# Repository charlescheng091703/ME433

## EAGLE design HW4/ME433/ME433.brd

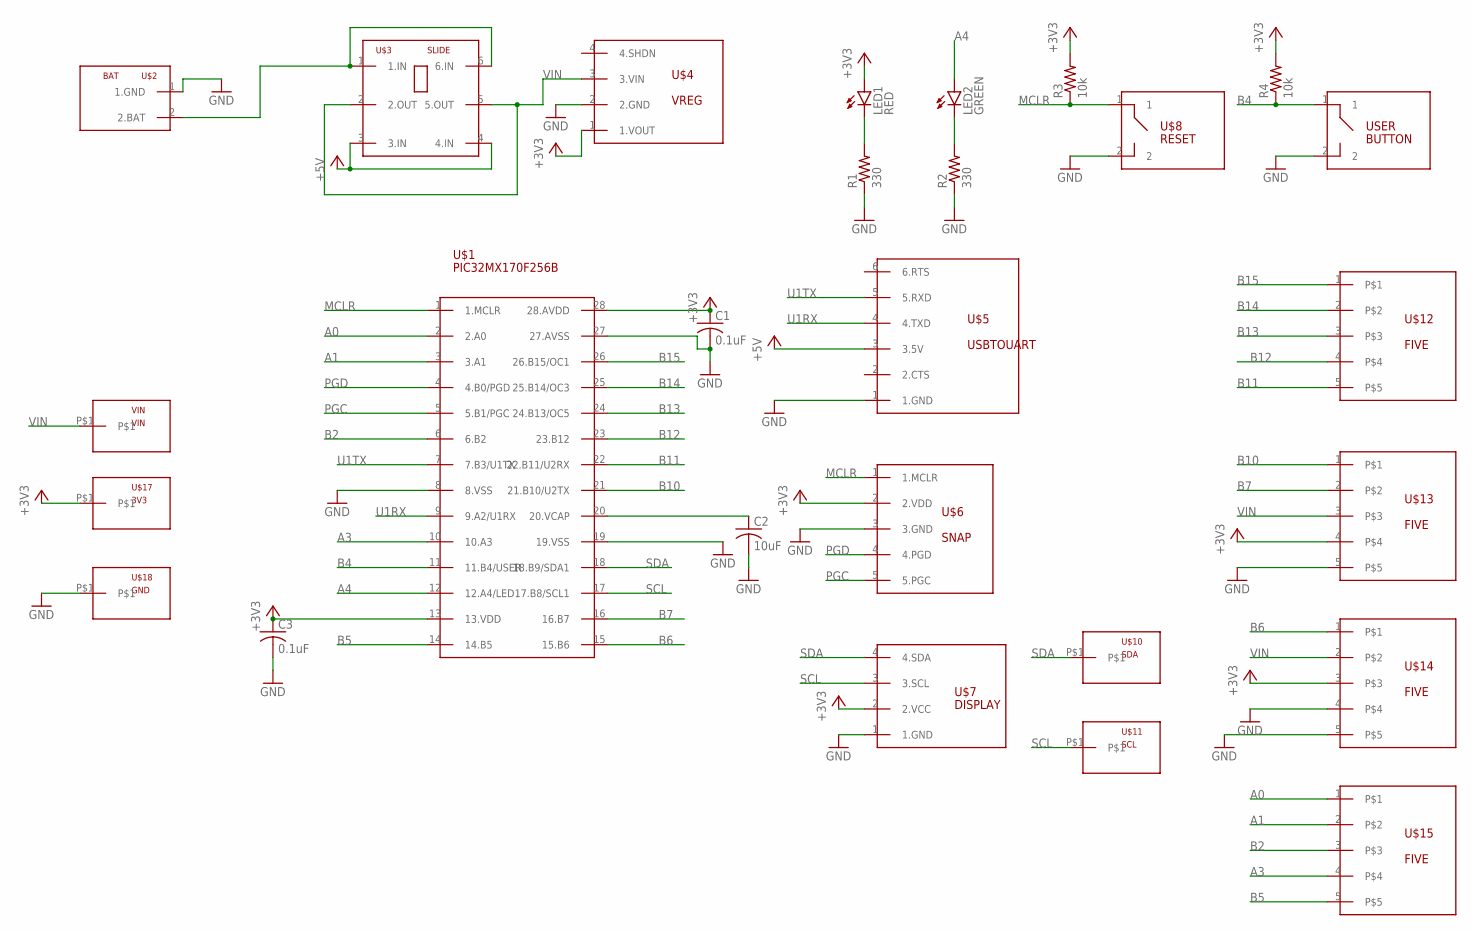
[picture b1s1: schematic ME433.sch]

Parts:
C1, C3: 0.1uF; C025-024X044
C2: 10uF; C025-024X044
LED1: RED; LED3MM
LED2: GREEN; LED3MM
R1, R2: 330; 0207/7
R3, R4: 10k; 0207/7
U$1: PIC32MX170F256B; DIL28-3
U$2: BAT
U$3: SLIDE
U$4: VREG
U$5: USBTOUART
U$6: SNAP
U$7: DISPLAY
U$8: RESET; BUTTON
U$10: SDA; 1
U$11: SCL; 1
U$12, U$13, U$14, U$15: FIVE
U$17: 3V3; 1
U$18: GND; 1
USER: BUTTON
VIN: VIN; 1

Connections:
+3V3: C1.1, C3.1, LED1.A, R3.2, R4.2, U$1.13 (13.VDD), U$1.28 (28.AVDD), U$4.1 (1.VOUT), U$6.2 (2.VDD), U$7.2 (2.VCC), U$13.4, U$14.3, U$17.P$1
+5V: U$3.3 (3.IN), U$3.4 (4.IN), U$5.3 (3.5V)
A0: U$1.2 (2.A0), U$15.1
A1: U$1.3 (3.A1), U$15.2
A3: U$1.10 (10.A3), U$15.4
A4: LED2.A, U$1.12 (12.A4/LED)
B2: U$1.6 (6.B2), U$15.3
B4: R4.1, U$1.11 (11.B4/USER), USER.1
B5: U$1.14 (14.B5), U$15.5
B6: U$1.15 (15.B6), U$14.1
B7: U$1.16 (16.B7), U$13.2
B10: U$1.21 (21.B10/U2TX), U$13.1
B11: U$1.22 (22.B11/U2RX), U$12.5
B12: U$1.23 (23.B12), U$12.4
B13: U$1.24 (24.B13/OC5), U$12.3
B14: U$1.25 (25.B14/OC3), U$12.2
B15: U$1.26 (26.B15/OC1), U$12.1
GND: C1.2, C2.2, C3.2, R1.1, R2.1, U$1.8 (8.VSS), U$1.19 (19.VSS), U$1.27 (27.AVSS), U$2.1 (1.GND), U$4.2 (2.GND), U$5.1 (1.GND), U$6.3 (3.GND), U$7.1 (1.GND), U$8.2, U$13.5, U$14.4, U$14.5, U$18.P$1, USER.2
MCLR: R3.1, U$1.1 (1.MCLR), U$6.1 (1.MCLR), U$8.1
unnamed: C2.1, U$1.20 (20.VCAP)
unnamed: U$2.2 (2.BAT), U$3.1 (1.IN), U$3.6 (6.IN)
unnamed: LED1.K (C), R1.2
unnamed: LED2.K (C), R2.2
PGC: U$1.5 (5.B1/PGC), U$6.5 (5.PGC)
PGD: U$1.4 (4.B0/PGD), U$6.4 (4.PGD)
SCL: U$1.17 (17.B8/SCL1), U$7.3 (3.SCL), U$11.P$1
SDA: U$1.18 (18.B9/SDA1), U$7.4 (4.SDA), U$10.P$1
U1RX: U$1.9 (9.A2/U1RX), U$5.4 (4.TXD)
U1TX: U$1.7 (7.B3/U1TX), U$5.5 (5.RXD)
VIN: U$3.2 (2.OUT), U$3.5 (5.OUT), U$4.3 (3.VIN), U$13.3, U$14.2, VIN.P$1

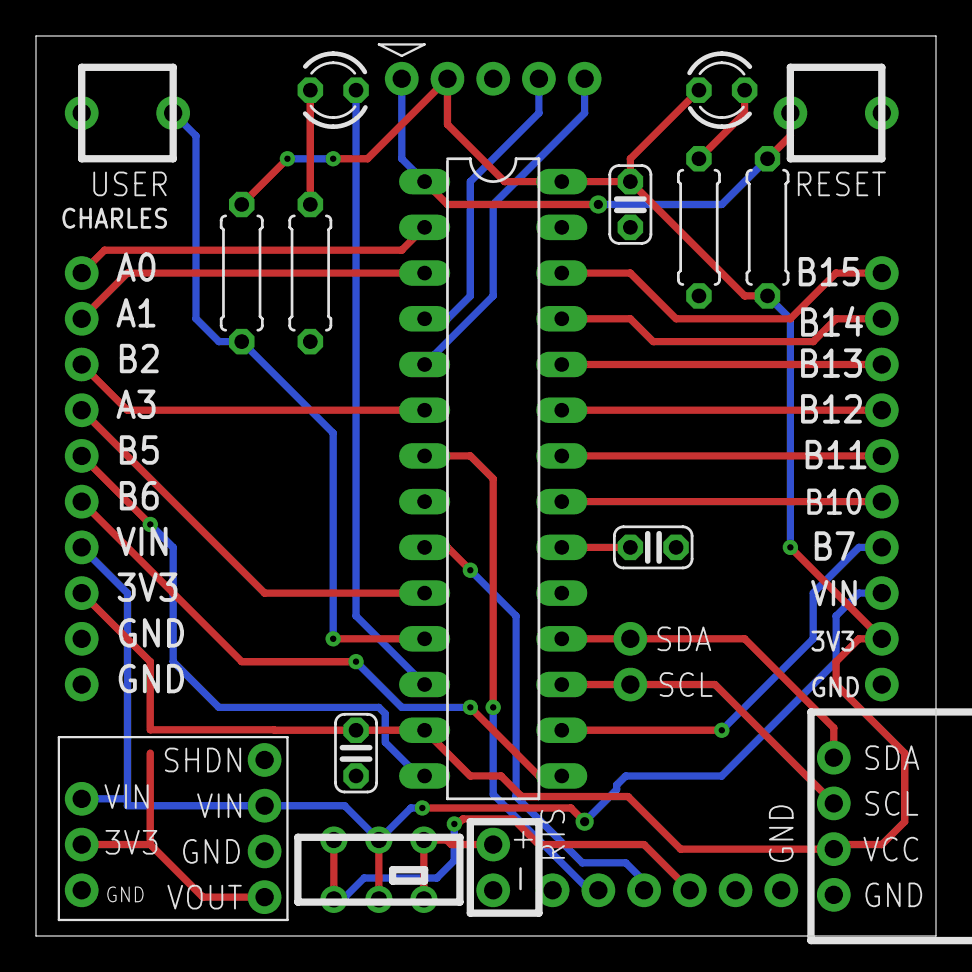
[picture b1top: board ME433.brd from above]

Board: 2 copper layers, 50.0 x 50.0 mm, 27 parts (0 on the bottom side), 30 nets.

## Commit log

2022-04-03 Upload HW2 Folder
    Creation of HW2 folder
2022-04-05 Upload HW3 Folder to Github
    Upload HW3
2022-04-06 Small edits
    Updated comments
2022-04-17 Add HW4
2022-04-19 Add HW5
2022-04-21 Add HW6
2022-04-24 Add HW7
2022-05-15 Upload HW8
    Add HW8
2022-05-15 Upload HW9
2022-05-15 Upload HW10
2022-05-15 Fixed typo
2022-05-17 Start HW11
2022-05-17 Add videos
2022-05-18 Update HW11
2022-06-10 Upload HW12 Pictures
